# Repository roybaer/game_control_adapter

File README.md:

# Game Control Adapter

This is an untested design for an 8-bit ISA card with gameport.
It avoids the use of the obsolete NE558 quad timer IC and uses two NE556 dual timers, instead.

## Front view

This picture shows the front of the card.

## License

The following license applies to the files in this repository:

This work is licensed under the Creative Commons Attribution-ShareAlike 4.0 International License. To view a copy of this license, visit http://creativecommons.org/licenses/by-sa/4.0/ or send a letter to Creative Commons, PO Box 1866, Mountain View, CA 94042, USA.

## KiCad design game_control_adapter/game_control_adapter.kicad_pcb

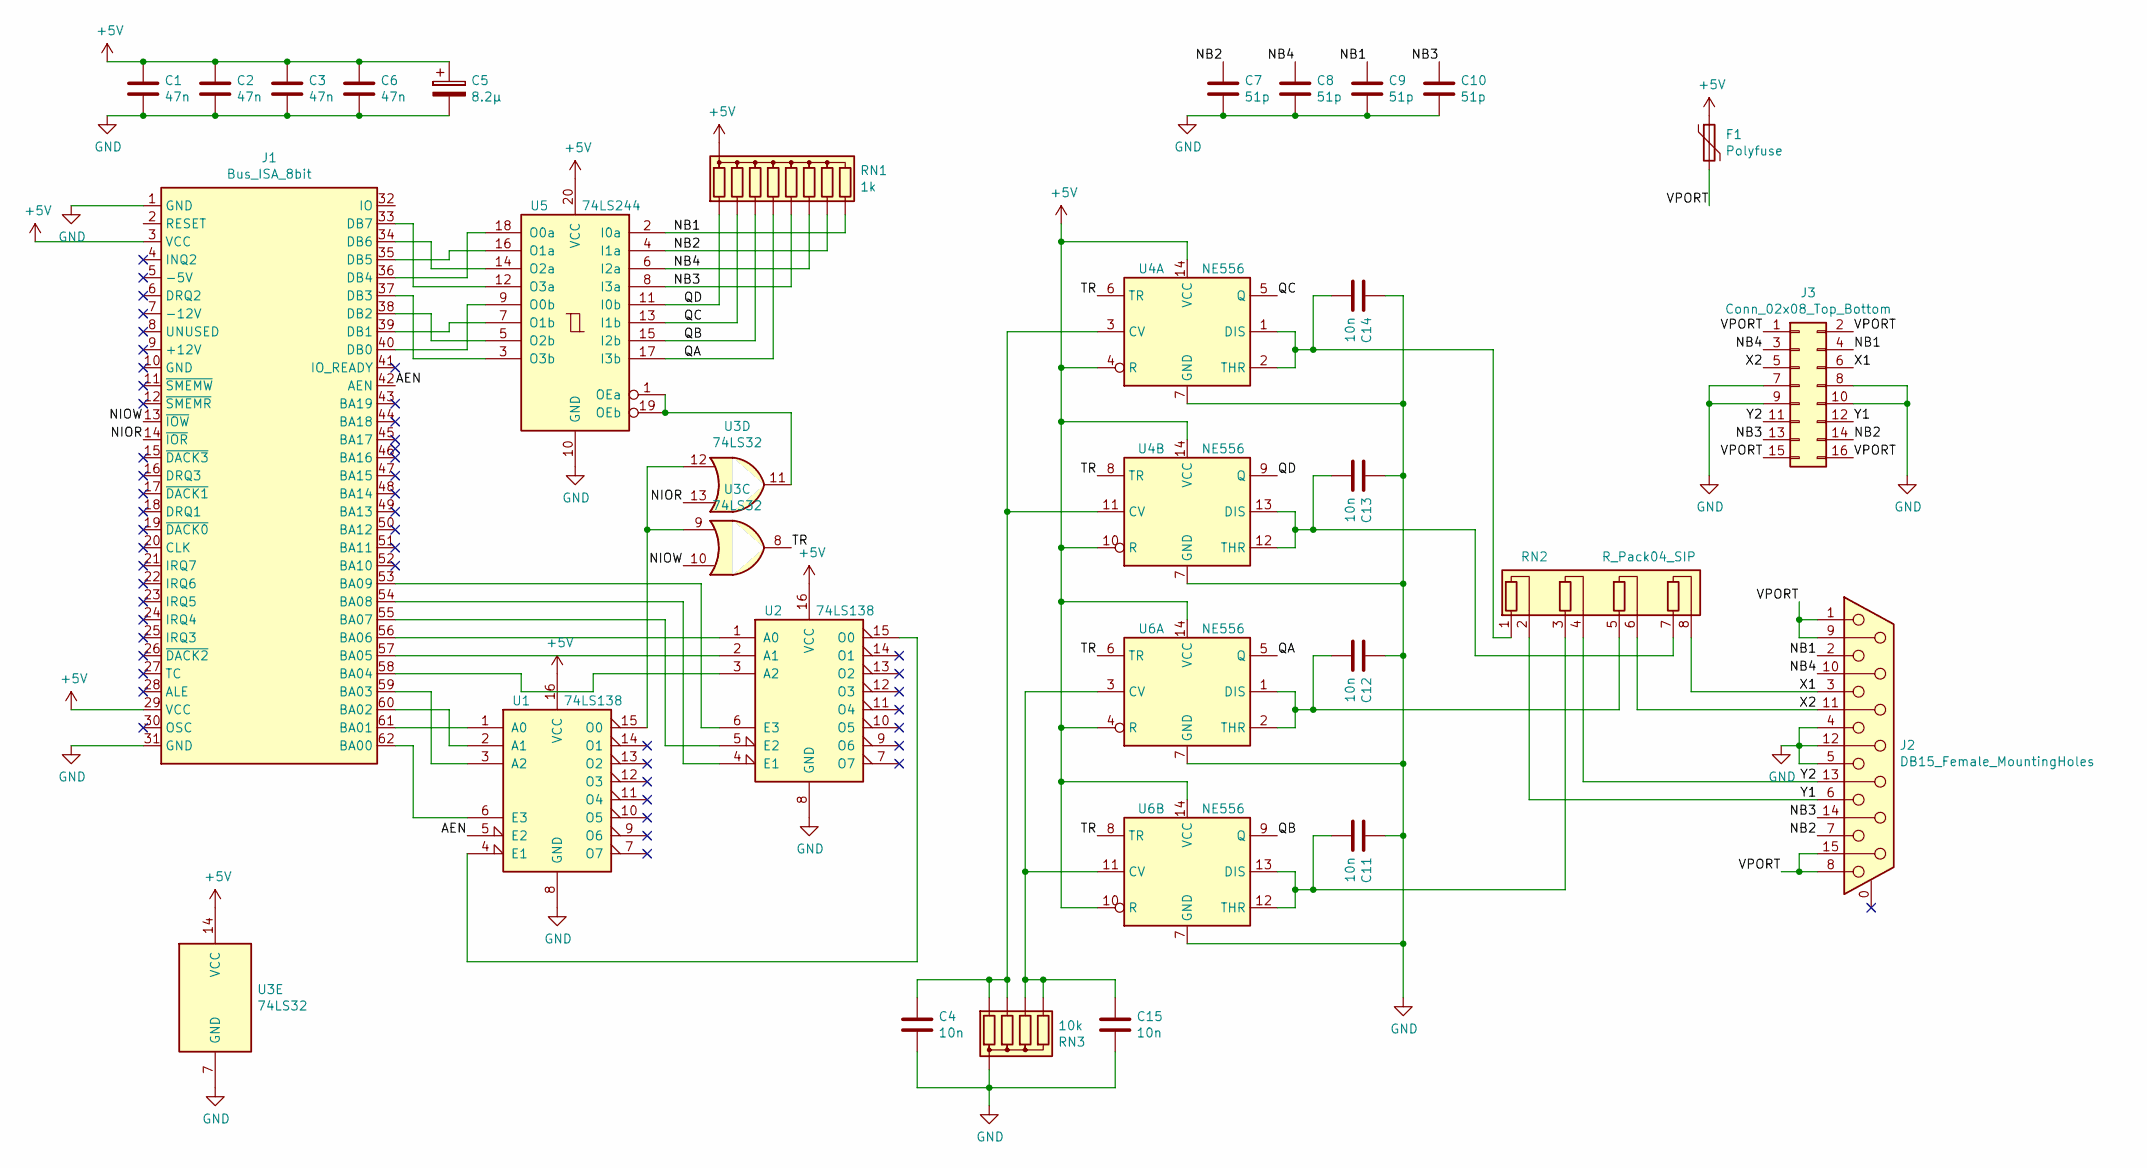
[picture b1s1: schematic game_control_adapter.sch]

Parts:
C1, C2, C3, C6: 47n; C_Disc_D4.7mm_W2.5mm_P5.00mm
C4, C11, C12, C13, C14, C15: 10n; C_Disc_D4.7mm_W2.5mm_P5.00mm
C5: 8.2µ; CP_Radial_D5.0mm_P2.50mm
C7, C8, C9, C10: 51p; C_Disc_D4.7mm_W2.5mm_P5.00mm
F1: Polyfuse; C_Disc_D5.0mm_W2.5mm_P5.00mm
J1: Bus_ISA_8bit; BUS_AT
J2: DB15_Female_MountingHoles; DSUB-15_Female_Horizontal_P2.77x2.84mm_EdgePinOffset9.90mm_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
J3: Conn_02x08_Top_Bottom; IDC-Header_2x08_P2.54mm_Vertical
RN1: 1k; R_Array_SIP9
RN2: R_Pack04_SIP; R_Array_SIP8
RN3: 10k; R_Array_SIP5
U1, U2: 74LS138; DIP-16_W7.62mm
U3: 74LS32; DIP-14_W7.62mm
U4, U6: NE556; DIP-14_W7.62mm
U5: 74LS244; DIP-20_W7.62mm

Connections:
+5V: C1.1, C2.1, C3.1, C5.1, C6.1, F1.1, J1.3 (VCC), J1.29 (VCC), RN1.1 (common), U1.16 (VCC), U2.16 (VCC), U3.14 (VCC), U4.4 (R), U4.10 (R), U4.14 (VCC), U5.20 (VCC), U6.4 (R), U6.10 (R), U6.14 (VCC)
/AEN: J1.42 (AEN), U1.5 (E2)
/NB1: C9.1, J2.2, J3.4, RN1.9 (R8), U5.2 (I0a)
/NB2: C7.1, J2.7, J3.14, RN1.8 (R7), U5.4 (I1a)
/NB3: C10.1, J2.14, J3.13, RN1.6 (R5), U5.8 (I3a)
/NB4: C8.1, J2.10, J3.3, RN1.7 (R6), U5.6 (I2a)
/NIOR: J1.14 (~IOR), U3.13
/NIOW: J1.13 (~IOW), U3.10
/QA: RN1.5 (R4), U5.17 (I3b), U6.5 (Q)
/QB: RN1.4 (R3), U5.15 (I2b), U6.9 (Q)
/QC: RN1.3 (R2), U4.5 (Q), U5.13 (I1b)
/QD: RN1.2 (R1), U4.9 (Q), U5.11 (I0b)
/TR: U3.8, U4.6 (TR), U4.8 (TR), U6.6 (TR), U6.8 (TR)
/VPORT: F1.2, J2.1, J2.8, J2.9, J2.15, J3.1, J3.2, J3.15, J3.16
/X1: J2.3, J3.6, RN2.8 (R4.2)
/X2: J2.11 (P111), J3.5, RN2.6 (R3.2)
/Y1: J2.6, J3.12, RN2.2 (R1.2)
/Y2: J2.13, J3.11, RN2.4 (R2.2)
GND: C1.2, C2.2, C3.2, C4.2, C5.2, C6.2, C7.2, C8.2, C9.2, C10.2, C11.1, C12.1, C13.1, C14.1, C15.2, J1.1 (GND), J1.31 (GND), J2.4, J2.5, J2.12, J3.7, J3.8, J3.9, J3.10, RN3.1 (common), U1.8 (GND), U2.8 (GND), U3.7 (GND), U4.7 (GND), U5.10 (GND), U6.7 (GND)
unnamed: C4.1, RN3.2 (R1), RN3.3 (R2), U4.3 (CV), U4.11 (CV)
unnamed: C11.2, RN2.3 (R2.1), U6.12 (THR), U6.13 (DIS)
unnamed: C12.2, RN2.5 (R3.1), U6.1 (DIS), U6.2 (THR)
unnamed: C13.2, RN2.7 (R4.1), U4.12 (THR), U4.13 (DIS)
unnamed: C14.2, RN2.1 (R1.1), U4.1 (DIS), U4.2 (THR)
unnamed: C15.1, RN3.4 (R3), RN3.5 (R4), U6.3 (CV), U6.11 (CV)
unnamed: J1.33 (DB7), U5.12 (O3a)
unnamed: J1.34 (DB6), U5.14 (O2a)
unnamed: J1.35 (DB5), U5.16 (O1a)
unnamed: J1.36 (DB4), U5.18 (O0a)
unnamed: J1.37 (DB3), U5.3 (O3b)
unnamed: J1.38 (DB2), U5.5 (O2b)
unnamed: J1.39 (DB1), U5.7 (O1b)
unnamed: J1.40 (DB0), U5.9 (O0b)
unnamed: J1.53 (BA09), U2.6 (E3)
unnamed: J1.54 (BA08), U2.4 (E1)
unnamed: J1.55 (BA07), U2.5 (E2)
unnamed: J1.56 (BA06), U2.1 (A0)
unnamed: J1.57 (BA05), U2.2 (A1)
unnamed: J1.58 (BA04), U2.3 (A2)
unnamed: J1.59 (BA03), U1.3 (A2)
unnamed: J1.60 (BA02), U1.2 (A1)
unnamed: J1.61 (BA01), U1.1 (A0)
unnamed: J1.62 (BA00), U1.6 (E3)
unnamed: U1.4 (E1), U2.15 (O0)
unnamed: U1.15 (O0), U3.9, U3.12
unnamed: U3.11, U5.1 (OEa), U5.19 (OEb)

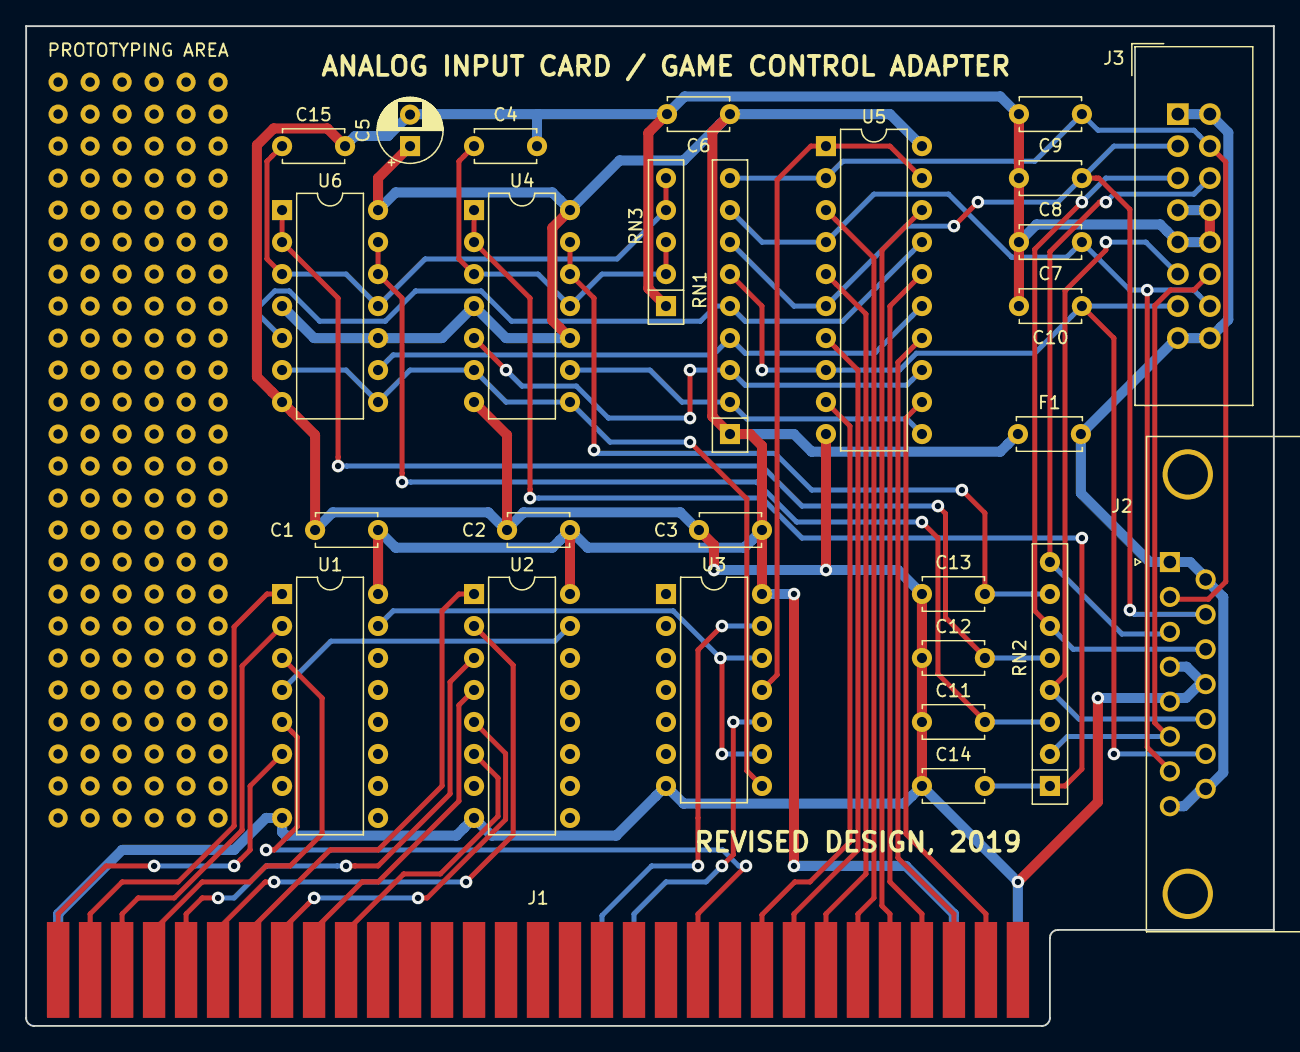
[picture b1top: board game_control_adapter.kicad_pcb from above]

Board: 2 copper layers, 99.1 x 79.4 mm, 28 parts (0 on the bottom side), 46 nets.
